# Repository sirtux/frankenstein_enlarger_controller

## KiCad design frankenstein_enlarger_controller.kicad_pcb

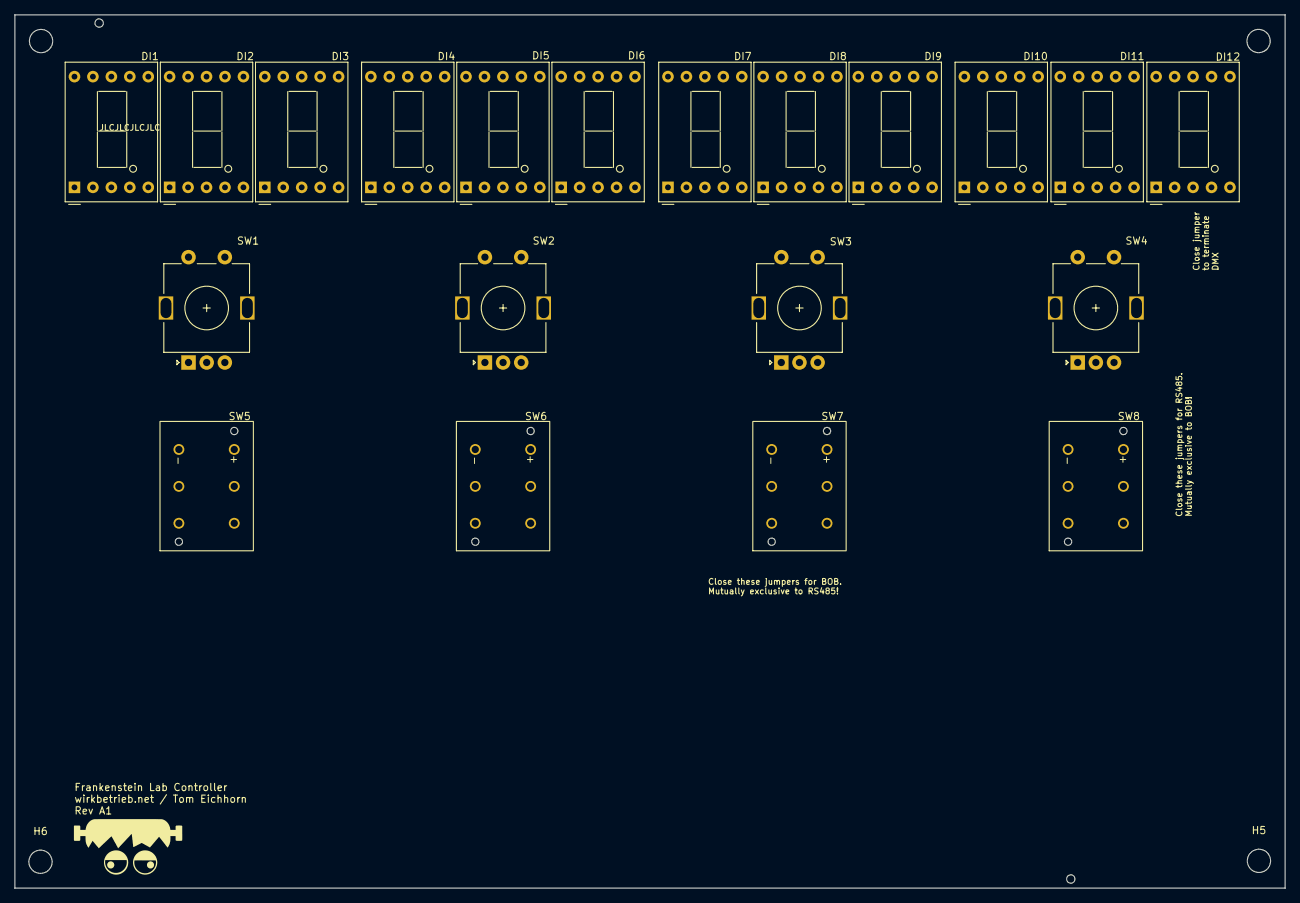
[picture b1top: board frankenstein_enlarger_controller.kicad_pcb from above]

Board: 4 copper layers, 174.8 x 120.2 mm, 26 parts (0 on the bottom side), 2 nets, no tracks yet.

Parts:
DI1, DI2, DI3, DI4, DI5, DI6, DI7, DI8, DI9, DI10, DI11, DI12: D168K; D1X8K
H1, H2: MountingHole; ToolingHole_JLCSMT
H3, H4, H5, H6: MountingHole; MountingHole_3.2mm_M3
SW1, SW2, SW3, SW4: RotaryEncoder_Switch; RotaryEncoder_Alps_EC11E-Switch_Vertical_H20mm
SW5, SW6, SW7, SW8: E-SWITCH 5501M; 5501M

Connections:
+3.3V: SW5.1, SW6.1, SW7.1, SW8.1
GND: DI1.3 (CC), DI1.8 (CC), DI2.3 (CC), DI2.8 (CC), DI3.3 (CC), DI3.8 (CC), DI4.3 (CC), DI4.8 (CC), DI5.3 (CC), DI5.8 (CC), DI6.3 (CC), DI6.8 (CC), DI7.3 (CC), DI7.8 (CC), DI8.3 (CC), DI8.8 (CC), DI9.3 (CC), DI9.8 (CC), DI10.3 (CC), DI10.8 (CC), DI11.3 (CC), DI11.8 (CC), DI12.3 (CC), DI12.8 (CC), SW1.C, SW1.S2, SW2.C, SW2.S2, SW3.C, SW3.S2, SW4.C, SW4.S2, SW5.-, SW6.-, SW7.-, SW8.-

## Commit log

2023-05-01 Added .gitignore
2023-05-01 Initial version, parts placement except RS485
2023-05-01 First maybe complete version?
2023-05-02 Add all backups to .gitignore
2023-05-02 Implemented fixes/changes after @manawyrm review
2023-05-14 Baseboard Software
2023-05-22 Rotary Stuff
2023-05-28 Software fixes
2023-06-24 Various stuff I've forgotten to commit
2023-08-13 Consolidated Hardware on single board
2023-08-22 Tie VBUS_FET_EN and SAFE_PWR_EN together
